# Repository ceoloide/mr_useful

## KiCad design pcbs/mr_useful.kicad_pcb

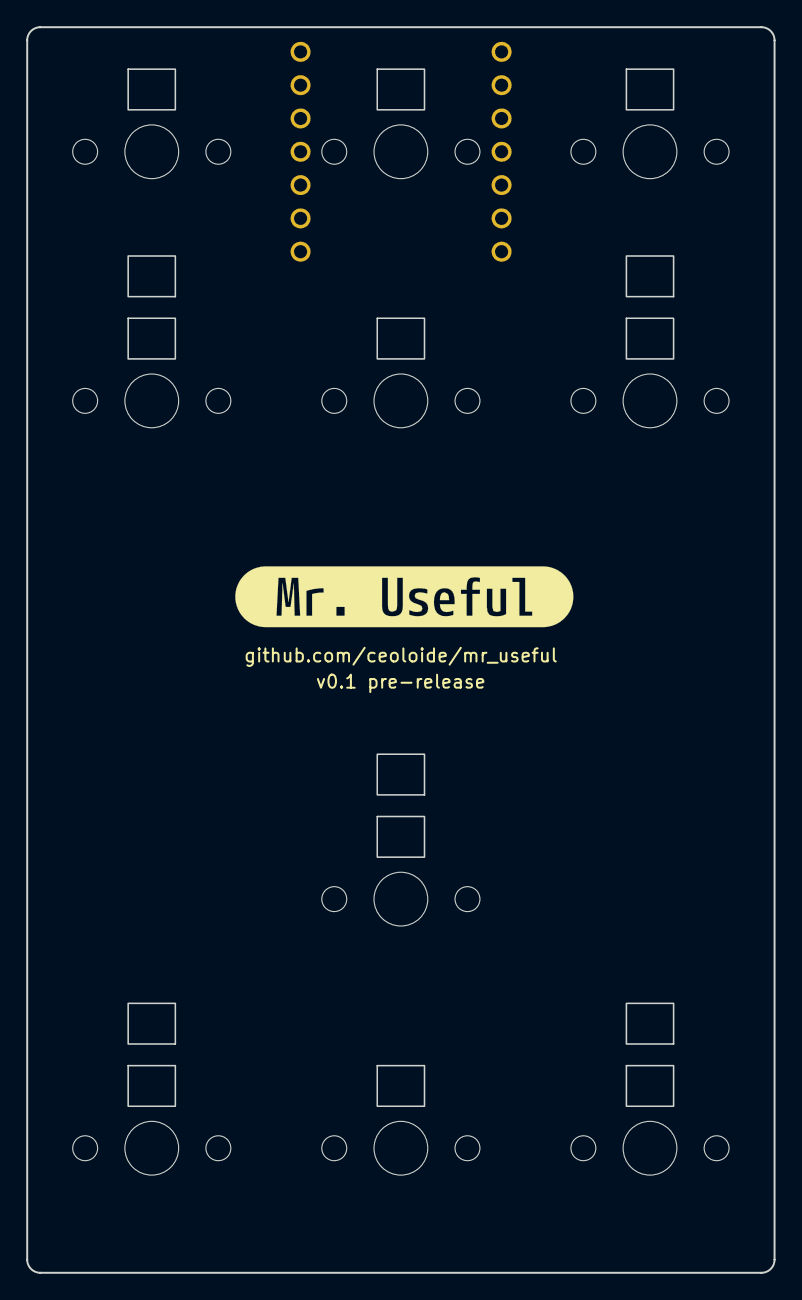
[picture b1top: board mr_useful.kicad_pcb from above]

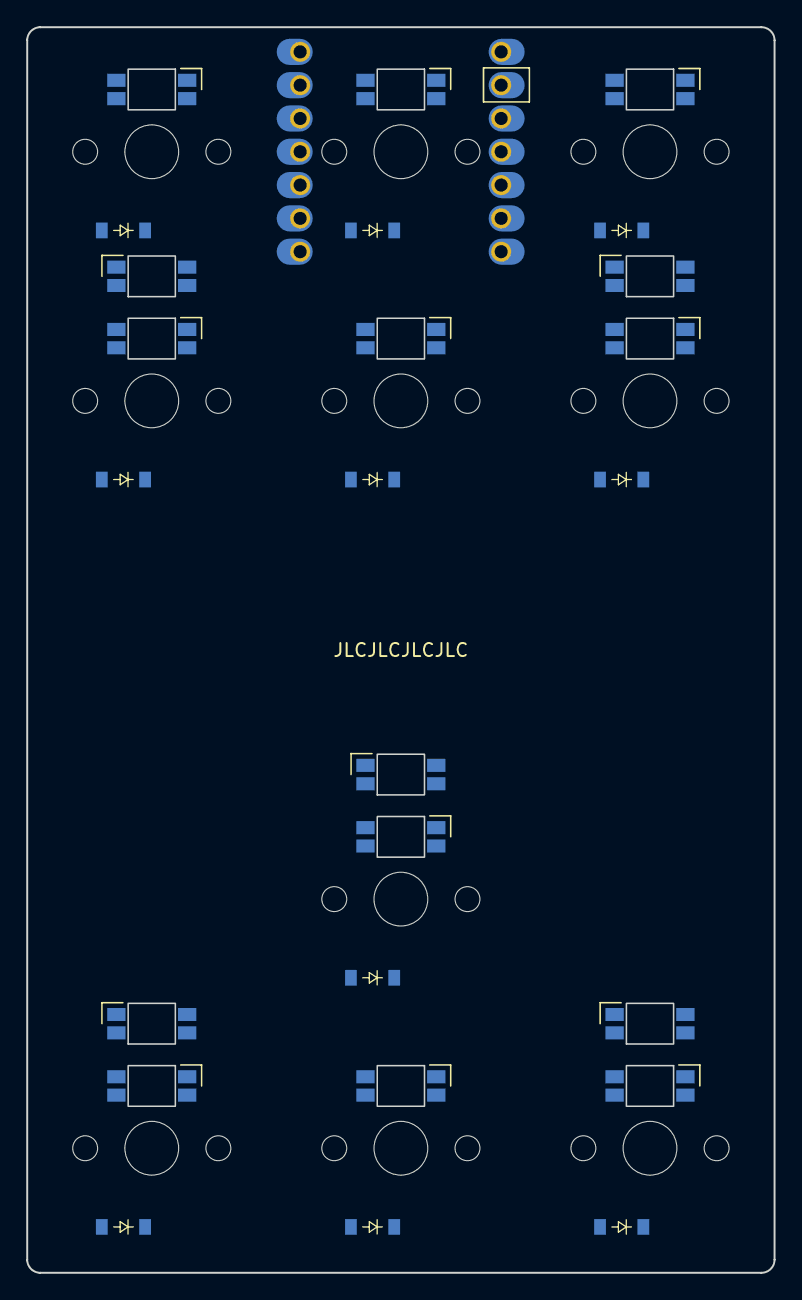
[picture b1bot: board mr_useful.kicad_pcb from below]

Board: 2 copper layers, 57.0 x 95.0 mm, 37 parts (36 on the bottom side), 21 nets, no tracks yet.

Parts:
D1, D2, D3, D4, D5, D6, D7, D8, D9, D10: diode_tht_sod123
LED1, LED2, LED3, LED4, LED5, LED6, LED7, LED8, LED9, LED10: led_SK6812mini-e (per-keysingle-side)
LED11, LED12, LED13, LED14, LED15: led_SK6812mini-e (underglowsingle-side)
LOGO1: logo_mr_useful
MCU1: Seeeduino XIAO-MOUDLE14P-2.54-21X17.8MM tht maybe
S1, S2, S3, S4, S5, S6, S7, S8, S9, S10: switch_mx

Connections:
GND: LED1.3, LED2.3, LED3.3, LED4.3, LED5.3, LED6.3, LED7.3, LED8.3, LED9.3, LED10.3, LED11.3, LED12.3, LED13.3, LED14.3, LED15.3, MCU1.GND
LED: LED8.4, MCU1.P3
LED_1: LED6.4, LED8.2
LED_2: LED5.4, LED6.2
LED_3: LED1.4, LED5.2
LED_4: LED1.2, LED2.4
LED_5: LED2.2, LED3.4
LED_6: LED3.2, LED7.4
LED_7: LED7.2, LED10.4
LED_8: LED9.4, LED10.2
LED_9: LED4.4, LED9.2
LED_10: LED4.2, LED13.4
R0: D1.1, D2.1, D4.1, MCU1.P10
R1: D3.1, MCU1.P9
R3: D5.1, D7.1, D9.1, MCU1.P7
R4: D6.1, D8.1, D10.1
ULED_1: LED12.4, LED13.2
ULED_2: LED11.4, LED12.2
ULED_3: LED11.2, LED14.4
ULED_4: LED14.2, LED15.4
VCC: LED1.1, LED2.1, LED3.1, LED4.1, LED5.1, LED6.1, LED7.1, LED8.1, LED9.1, LED10.1, LED11.1, LED12.1, LED13.1, LED14.1, LED15.1, MCU1.3V3

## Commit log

2023-06-25 Add gerbers
2023-06-28 Update XIAO SAMD21 footprint
2023-06-28 Fix missing module closing bracket
2023-06-28 Fix net definitions
2023-06-28 Fix compatibility with KiCad 5
2023-06-28 Switch to set-blue-enig rendering style
2023-06-28 Fix VCC net name and generate outputs
2023-06-28 Update diode footprint to be on one side only
2023-06-28 Add cutout to access USB-C port
2023-06-29 Update outlines to use `expand`
2023-06-30 Update outlines with parameters
2023-06-30 Update build script to include top / bottom plates
2023-06-30 Update assets
2023-07-02 Add user drawing to show XIAO footprint
2023-07-02 Rename XIAO footprint file
2023-07-02 Update combo diode footprint to be reversible
2023-07-02 Update config to use new diode options
2023-07-02 Add logo and reference
2023-10-16 Remove `fill` from footprint
2023-10-16 Update net classes
2023-10-16 Change text thickness to match JLCPC minimum
2023-10-16 Rotate underglow LEDs to facilitate routing
2023-10-16 Add routed board to GitHub Action outputs
2023-10-16 Change routing rules to allow 0.15mm traces
2023-10-16 Ignore KiBot outputs
2023-10-16 Update KiBot to run DRC
2023-10-16 Add JLCPCB order number text
2023-10-16 Ignore logs folder
2023-10-16 Renove unrouted from artifact name
2023-10-17 Add Freerouting rules
2023-10-17 Add Freerouting rules and max passes
2023-10-17 Add max passes to autorouting
2023-10-17 Add ignores for track width
2023-10-17 Add GND/PWR to Freerouting rules
2023-10-18 Initial nix shell
2023-10-18 Simplify KiBot yaml files
2023-10-18 Update Freerouting rules
2023-10-19 Fix wrong KiBot config in GitHub Actions
2023-10-19 Align autorouting workflow to Corney Island
2023-10-19 Bumb node up to v18
2023-10-19 Update npm packages
2023-10-20 Build Freerouting from "HEAD" along with 1.7.0
2023-10-20 Fix wrong package name attribute
2023-10-20 Update rules with fixes and new defaults
2023-10-22 Update LED footprint
2023-10-22 Revert to Freerouting 1.0.0 CLI
2023-10-30 Reduce `smd_to_turn_gap` clearance
2023-10-30 Copy rules from Corney Island
2024-01-30 Update actions that depend on NodeJs 16
2024-01-30 Add centralized footprints submodule
2024-01-30 Align GitHub workflow to the Corney Island
2024-01-30 Bump ergogen to v4.0.5
2024-01-30 Update ergogen and npm packages
2024-01-30 Add ceoloide central footprints
2024-01-30 Switch to `ceoloide` footprints
2024-01-30 Use https repo url
2024-01-30 Remove infused-kim footprints
2024-01-30 Revert to freerouting-cli
2024-01-30 Hide solder paste on PCB images
2024-01-31 Update footprint submodule
2024-01-31 Format file
2024-02-01 Interim changes to the footprint
2024-02-01 Update submodule
2024-04-01 Update build pipeline to match the one from Corney Island (KiCad 8 support)
2024-04-01 Update footprint library
2024-04-01 Update GitHub Action to use KiCad Auto ki8 (KiCad 8)
2024-04-07 Update to latest ergogen version
2024-04-07 Update footprints library and artifacts
2024-11-14 Update footprints library
2024-11-14 Update build pipeline
2024-11-14 Update MX switch footprint
2024-11-14 Fix build.sh script
2024-11-18 Activate keepout around LEDs
2025-10-17 Update package-lock.json and package.json to include install script
2025-10-17 Update subproject commit for ceoloide footprint
